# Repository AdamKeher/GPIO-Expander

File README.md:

# GPIO Expander
An I2C controlled, breadboard friendly GPIO exansion board based on the Texas Instruments PCF8574 with builtin buttons and LED's for prototyping.
## PCB Layout

## About
The PCF8574 device provides general-purpose remote I/O expansion for most microcontroller families by way of the I2C interface (serial clock(SCL), serial data (SDA)].
The device features an 8-bit quasi-bidirectional I/O port (P0–P7), including latched outputs with highcurrent drive capability for directly driving LEDs. Each quasi-bidirectional I/O can be used as an input or output without the use of a data-direction control signal. At power on, the I/Os are high. In this mode, only a current source to VCC is active.

The board has builtin buttons and LED's to help quickly prototype solutions and is able to be mounted either vertically or horizontally.

A switchable jumper is provided to connect all tactiles switches to VCC or to GND.
## Features
* 2.5V to 6.0V operation
* Arduino Library
* 8 Builtin tactile switches
* 8 Builtin controllable LED's
* Breadboard friendly
* Based on the popular PCF8574 I2C IC
* Low Standby-Current Consumption of 10 μA Max
* Open-Drain Interrupt Output
* Compatible With Most Microcontrollers
* Latched Outputs With High-Current Drive
* Single Maskable output register for all IO ports

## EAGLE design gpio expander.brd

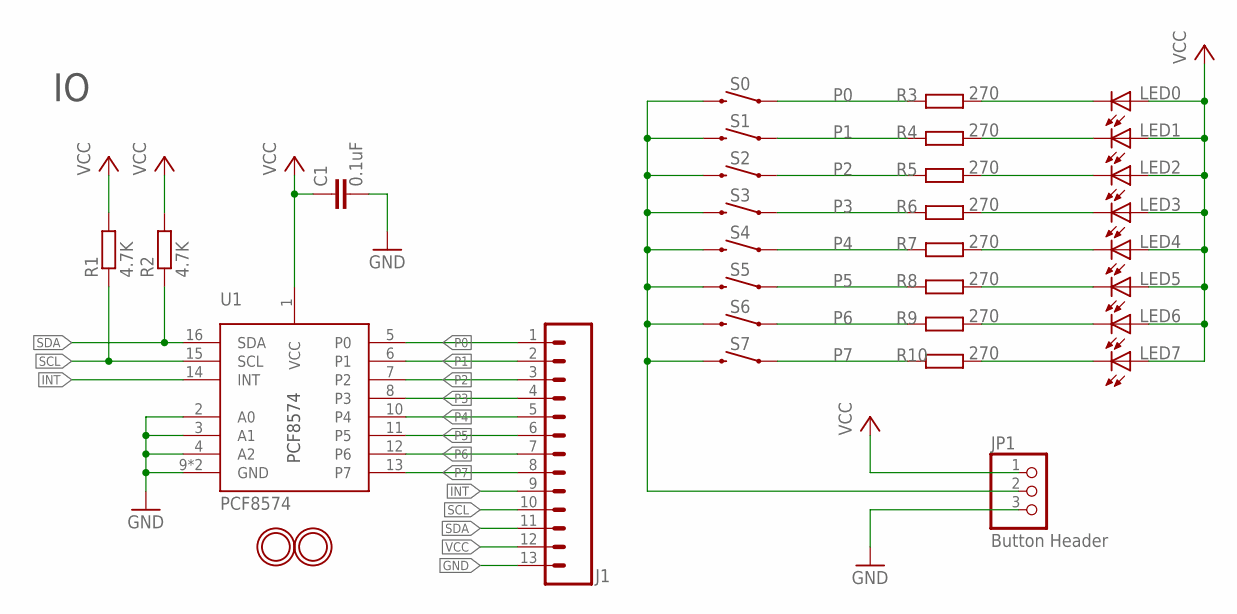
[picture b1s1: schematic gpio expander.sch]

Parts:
C1: 0.1uF; C0805K
J1: GPIO Expander Pins; 1X13_NO_SILK
JP1: Button Header; 1X03
LED0, LED1, LED2, LED3, LED4, LED5, LED6, LED7: GREEN; CHIP-LED0805
MH1, MH3: MOUNTINGHOLE2.5; MOUNTINGHOLE_2.5_PLATED
R1, R2: 4.7K; R0805
R3, R4, R5, R6, R7, R8, R9, R10: 270; R0805
S0, S1, S2, S3, S4, S5, S6, S7: MOMENTARY-SWITCH-SPST-SMD-4.6X2.8MM; TACTILE_SWITCH_SMD_4.6X2.8MM
U1: PCF8574; QFN-16-3MM

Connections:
GND: C1.2, J1.13, JP1.3, U1.2 (A0), U1.3 (A1), U1.4 (A2), U1.9 (GND), U1.P$1 (GND)
INT: J1.9, U1.14 (INT)
unnamed: JP1.2, S0.3 (2), S0.4 (2), S1.3 (2), S1.4 (2), S2.3 (2), S2.4 (2), S3.3 (2), S3.4 (2), S4.3 (2), S4.4 (2), S5.3 (2), S5.4 (2), S6.3 (2), S6.4 (2), S7.3 (2), S7.4 (2)
unnamed: LED0.C, R3.1
unnamed: LED1.C, R4.1
unnamed: LED2.C, R5.1
unnamed: LED3.C, R6.1
unnamed: LED4.C, R7.1
unnamed: LED5.C, R8.1
unnamed: LED6.C, R9.1
unnamed: LED7.C, R10.1
P0: J1.1, R3.2, S0.1, S0.2 (1), U1.5 (P0)
P1: J1.2, R4.2, S1.1, S1.2 (1), U1.6 (P1)
P2: J1.3, R5.2, S2.1, S2.2 (1), U1.7 (P2)
P3: J1.4, R6.2, S3.1, S3.2 (1), U1.8 (P3)
P4: J1.5, R7.2, S4.1, S4.2 (1), U1.10 (P4)
P5: J1.6, R8.2, S5.1, S5.2 (1), U1.11 (P5)
P6: J1.7, R9.2, S6.1, S6.2 (1), U1.12 (P6)
P7: J1.8, R10.2, S7.1, S7.2 (1), U1.13 (P7)
SCL: J1.10, R1.1, U1.15 (SCL)
SDA: J1.11, R2.1, U1.16 (SDA)
VCC: C1.1, J1.12, JP1.1, LED0.A, LED1.A, LED2.A, LED3.A, LED4.A, LED5.A, LED6.A, LED7.A, R1.2, R2.2, U1.1 (VCC)

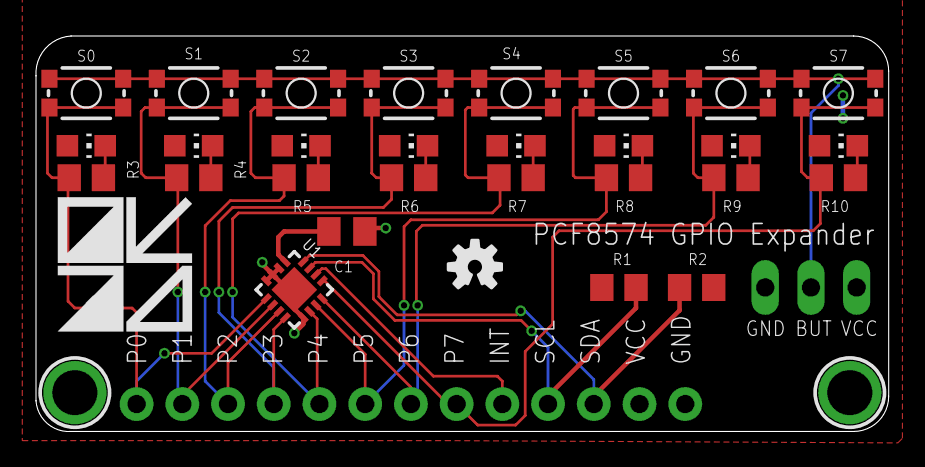
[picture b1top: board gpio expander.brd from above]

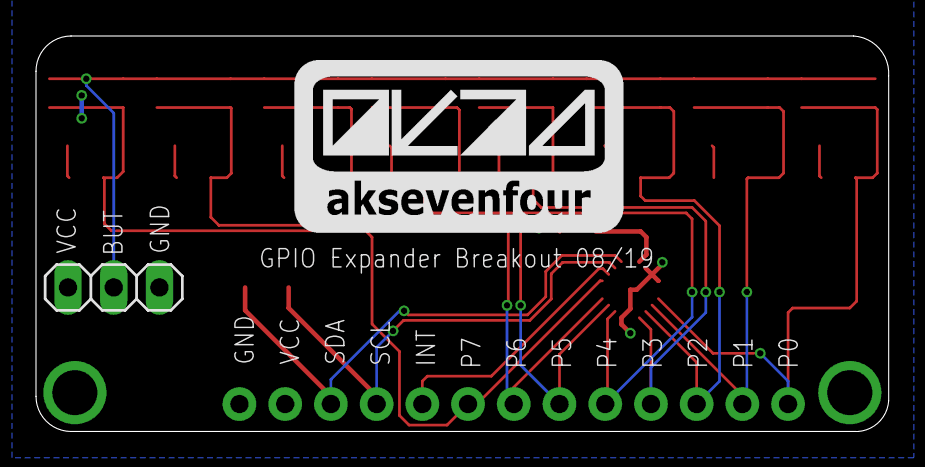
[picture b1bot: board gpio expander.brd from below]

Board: 2 copper layers, 47.4 x 22.0 mm, 35 parts (2 on the bottom side), 22 nets.

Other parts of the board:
U$1: AK74_LOGO_MEDIUM
U$2: AK74_LOGO_MEDIUM_TEXTONLY_SQUARE
U$3: OSHW-LOGO-S

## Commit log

2019-09-14 Removed redundant files

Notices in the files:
parts and their libraries:
microbuilder: This work is placed in the public domain, and may be freely used for commercial and non-commercial work with the following conditions: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
SparkFun-Switches: Licensing: Creative Commons ShareAlike 4.0 International - https://creativecommons.org/licenses/by-sa/4.0
